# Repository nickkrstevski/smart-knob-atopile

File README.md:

# smart-knob
Shoutout to Scott Bezek for creating this awesome open source haptic feedback wheel!
https://github.com/scottbez1/smartknob.git

# atopile
>ato install smartknob

This package contains adaptations of the smart knob designs captured in atopile code. atopile will help with jellybean component selection, board layout, versioning, collaboration..

Upon importing the smart knob package into your atopile project, you will find a complete netlist and accompanying layout that can be merged or connected into a larger design. atopile's component selection integrates directly wih the JLC component supplier, generating build outputs that can be directly sent to JLC and show up at your door assembled.

For example, I am creating a chess clock that uses the smart knob as a dial, and adds some leds/capacitive touch sensors to build upon the original design/layout.
https://github.com/nickkrstevski/chess-clock

# Structure
The Smart Knob design consists of 2 PCBAs, a BLDC motor, an LCD, and plenty of mechanical bits holding everything together. This project will contain a Smart Knob module that has 2 build target modules, "SmartKnobBase", and "SmartKnobScreen"

## SmartKnobBase
- ESP32-S3
- USB-C
- BLDC Driver
- Strain Sensor
- Ambient Light Sensor
- Magnetic Quadrature Encoder

## SmartKnobScreen
- Backlight FET/ballast resistor
- LCD Connections

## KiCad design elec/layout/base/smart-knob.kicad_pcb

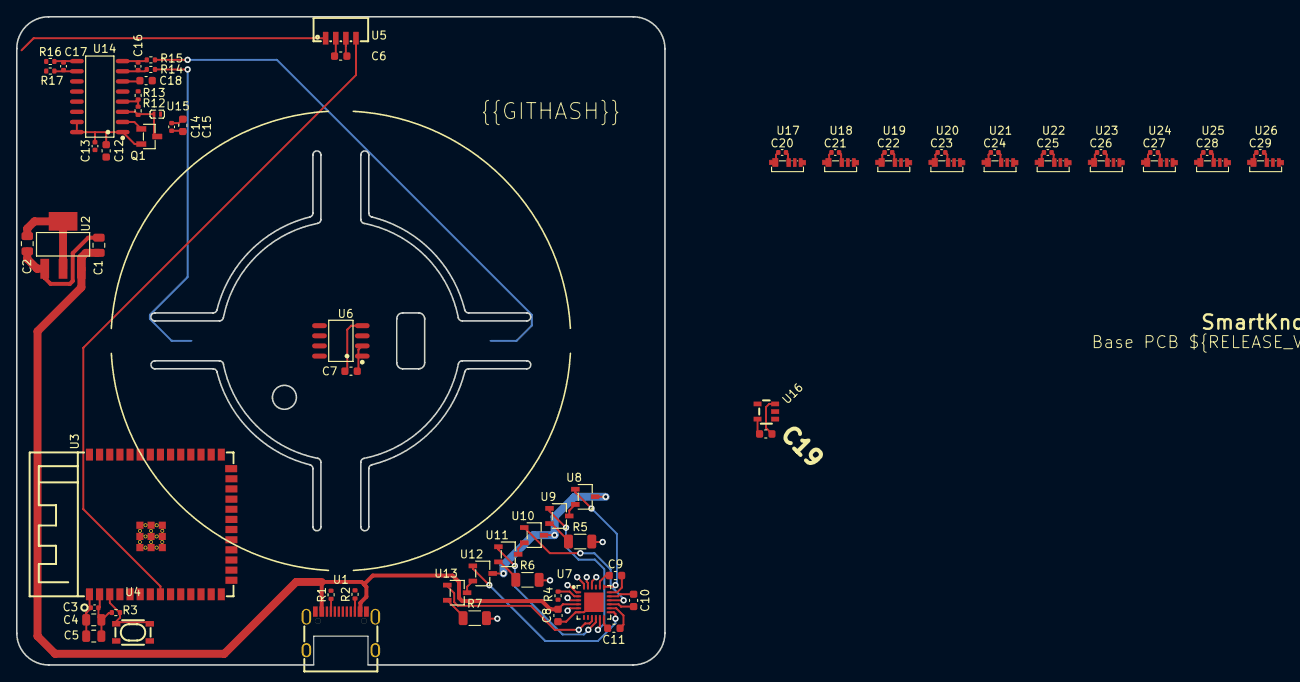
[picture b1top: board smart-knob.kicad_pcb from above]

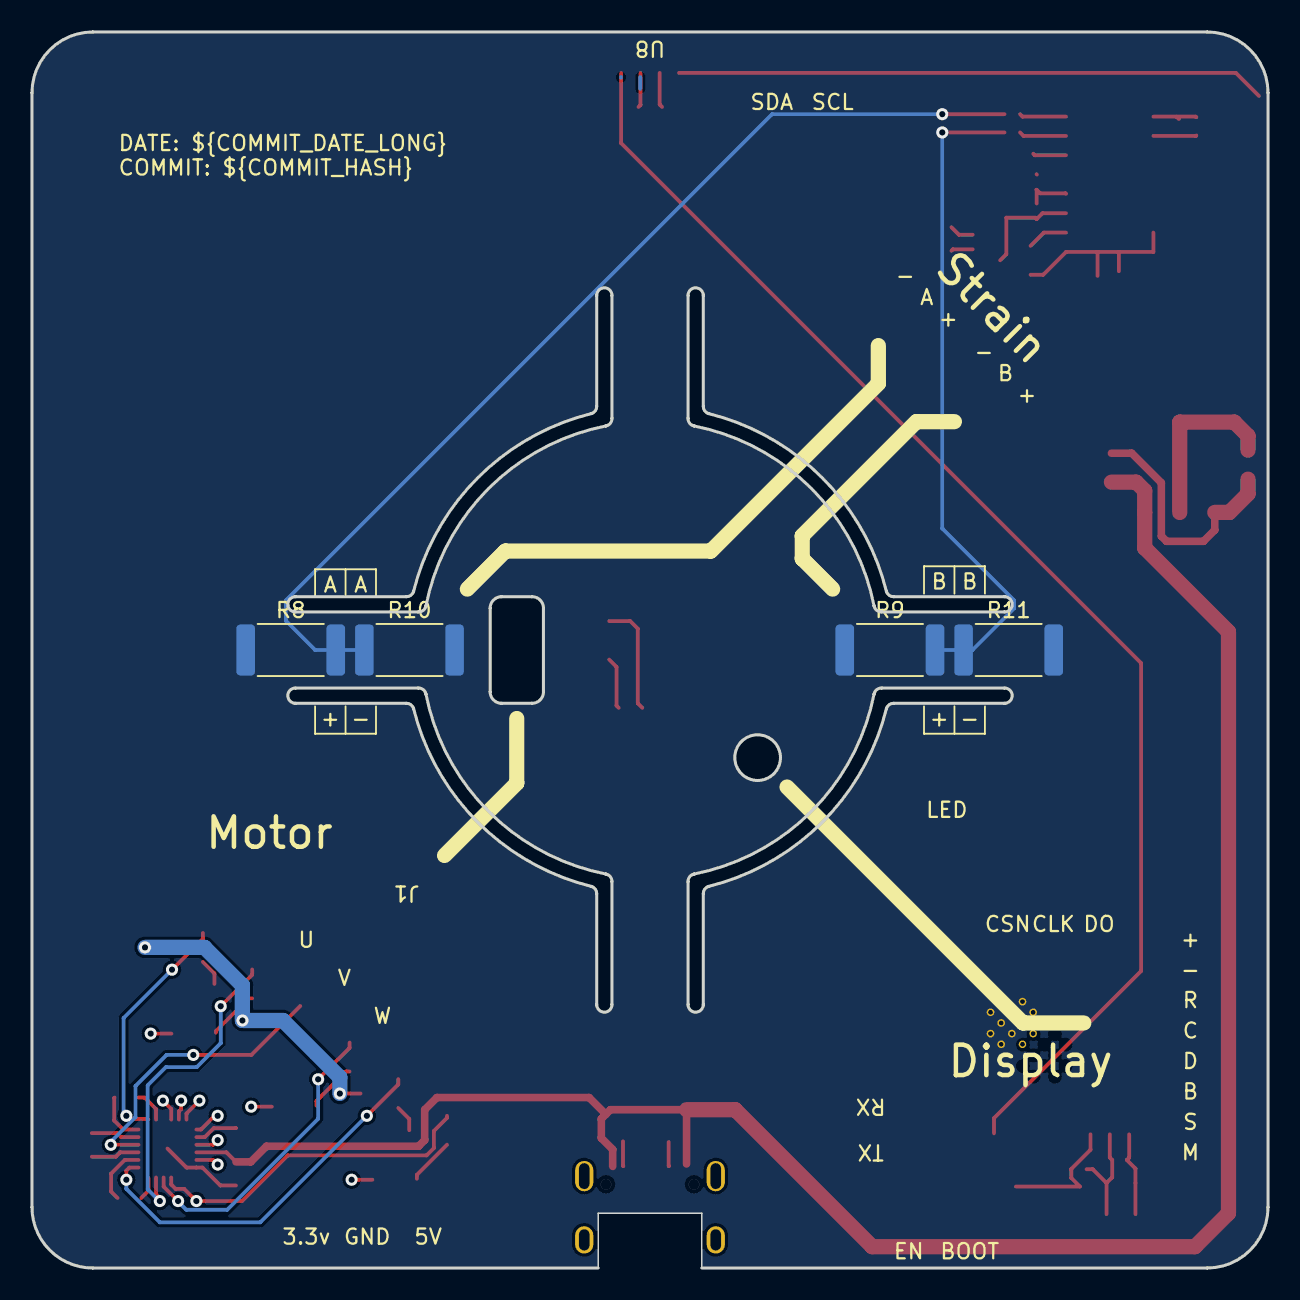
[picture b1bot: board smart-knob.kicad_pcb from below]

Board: 2 copper layers, 81.2 x 81.2 mm, 74 parts (4 on the bottom side), 64 nets.

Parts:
C1, C2, C4, C5: 25V 10uF X5R ±10% 0805 Multilayer Ceramic Capacit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; C0805
C3, C16, C17: 16V 100nF X7R ±10% 0402 Multilayer Ceramic Capaci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; C0402
C6, C7, C12, C15, C18, C19: 50V 100nF X7R ±10% 0603 Multilayer Ceramic Capaci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; C0603
C8, C9, C10, C11: 50V 1uF X5R ±10% 0603 Multilayer Ceramic Capacito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; C0603
C13, C14: 6.3V 10uF X5R ±20% 0402 Multilayer Ceramic Capaci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; C0402
C20, C21, C22, C23, C24, C25, C26, C27, C28, C29: 25V 1uF X5R ±10% 0402 Multilayer Ceramic Capacito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; C0402
Q1: SOT-23-3_L2.9-W1.3-P1.90-LS2.4-BR
R1, R2: 62.5mW Thick Film Resistors ±100ppm/℃ ±1% 5.1kΩ 0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; R0402
R3, R12: 62.5mW Thick Film Resistors ±100ppm/℃ ±1% 10kΩ 04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; R0402
R4: 62.5mW Thick Film Resistors ±100ppm/℃ ±1% 40.2kΩ 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; R0402
R5, R6, R7: 250mW Thick Film Resistors ±800ppm/℃ ±1% 1Ω 1206 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; R1206
R8, R9, R10, R11: 1W Thick Film Resistors ±100ppm/℃ ±5% 330Ω 2512 C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; R2512
R13: 62.5mW Thick Film Resistors ±100ppm/℃ ±1% 8.2kΩ 0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; R0402
R14, R15, R16, R17: 62.5mW Thick Film Resistors ±1% ±200ppm/℃ 100Ω 04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; R0402
U1: USB-C-SMD_KH-TYPE-C-16P
U2: SOT-223-3_L6.5-W3.4-P2.30-LS7.0-BR
U3: WIRELM-SMD_ESP32-S3-WROOM-1
U4: KEY-SMD_4P-L4.2-W3.2-P2.20-LS4.6
U5: SENSOR-SMD_EML7700-TT
U6: SOP-8_L4.9-W3.9-P1.27-LS6.0-BL
U7: VQFN-24_L4.0-W4.0-P0.50-TL-EP2.5
U8, U9, U10, U11, U12, U13: SOT-23-3_L2.9-W1.6-P1.90-LS2.8-BR
U14: SOP-16_L10.0-W3.9-P1.27-LS6.0-BL
U15: 3.3 +/- 0.99 (30%) microhenry; IND-SMD_L1.2-W0.7
U16: SOT-23-5_L2.9-W1.6-P0.95-LS2.8-BR
U17, U18, U19, U20, U21, U22, U23, U24, U25, U26: LED-SMD_4P-L4.0-W1.4_SK6805SIDE-S
Z5: dummy_keepouts; ViewKeepouts3d

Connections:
base: Q1.1, U14.2
cc1: R1.1, U1.A5
cc2: R2.1, U1.B5
clock: U3.38, U14.11
data: U3.31, U14.12
dm: U1.A7, U1.B7, U3.13
dp: U1.A6, U1.B6, U3.14
en: R3.2, U3.3, U4.1, U4.2
esp32s3.ic-sda: U3.8, U5.4
esp32s3.ic-sda-1: U3.7, U16.2
esp32s3.ic-vcc: U3.28, U7.3
esp32s3.ic-vcc-1: U3.26, U7.1
esp32s3.ic-vcc-2: U3.16, U7.22
esp32s3.ic-vcc-3: U3.11, U7.23
esp32s3.ic-vcc-4: R4.1, U3.10, U7.2
esp32s3.ic-vcc-5: U3.9, U7.24
gnd: R5.2, R6.2, R7.2
hba.nfet_low-source: R5.1, U9.2
hbb.nfet_low-source: R6.1, U11.2
hbc.nfet_low-source: R7.1, U13.2
inna: C16.2, R14.2, U14.7
innb: C17.2, R16.2, U14.9
inpa: C16.1, R15.2, U14.8
inpb: C17.1, R17.2, U14.10
io13: U3.21, U6.7
io14: U3.22, U6.8
io37: U3.30, U6.6
ldo3V3-vcc: C2.1, C3.1, C4.1, C5.1, C12.1, C13.1, Q1.2, R3.1, U2.2, U2.4, U3.2, U14.1, U14.15, U14.16
led1-vcc-1: U17.3, U18.4
led2-vcc: U18.3, U19.4
led3-vcc: U19.3, U20.4
led4-vcc: U20.3, U21.4
led5-vcc: U21.3, U22.4
led6-vcc: U22.3, U23.4
led7-vcc: U23.3, U24.4
led8-vcc: U24.3, U25.4
led9-vcc: U25.3, U26.4
light_sensor.ic-gnd: C6.2, U5.3
light_sensor.ic-vcc: C6.1, U5.2
n: R9.2, R11.1, R14.1
p: R8.2, R10.1, R15.1
phase_a: U8.2, U9.3
phase_b: U10.2, U11.3
phase_c: U12.2, U13.3
power_stage-vcc-1: U7.11, U9.1
power_stage-vcc-2: U7.10, U11.1
power_stage-vcc-3: U7.9, U13.1
power_stage-vcc-4: U7.19, U8.1
power_stage-vcc-5: U7.16, U10.1
power_stage-vcc-6: U7.13, U12.1
power_stage-vcc-7: C9.2, U7.18
power_stage-vcc-8: C10.2, U7.15
power_stage-vcc-9: C11.2, U7.12
power_stage.ic-vcc: C9.1, U7.20
power_stage.ic-vcc-1: C10.1, U7.17
power_stage.ic-vcc-2: C11.1, U7.14
scl: U3.12, U5.1
strain_adc.ic-vcc: Q1.3, R12.1, U14.3, U15.1
usbc-gnd: C1.2, C2.2, C3.2, C4.2, C5.2, C7.2, C8.2, C12.2, C13.2, C14.2, C15.2, C18.2, C19.2, C20.2, C21.2, C22.2, C23.2, C24.2, C25.2, C26.2, C27.2, C28.2, C29.2, R1.2, R2.2, R4.2, R10.2, R11.2, R13.2, U1.1, U1.2, U1.3, U1.4, U1.A1, U1.A12, U1.B1, U1.B12, U2.1, U3.1, U3.40, U3.41, U4.3, U4.4, U6.4, U7.6, U7.25, U14.5, U14.14, U16.3, U17.2, U18.2, U19.2, U20.2, U21.2, U22.2, U23.2, U24.2, U25.2, U26.2
usbc-vcc: C1.1, C7.1, C8.1, C19.1, C20.1, C21.1, C22.1, C23.1, C24.1, C25.1, C26.1, C27.1, C28.1, C29.1, U1.A4, U1.A9, U1.B4, U1.B9, U2.3, U6.1, U6.2, U7.4, U16.5, U17.1, U18.1, U19.1, U20.1, U21.1, U22.1, U23.1, U24.1, U25.1, U26.1
vbg: C18.1, U14.6
vcc: U8.3, U10.3, U12.3
vcc-1: C14.1, C15.1, R8.1, R9.1, U15.2
vfb: R12.2, R13.1, U14.4

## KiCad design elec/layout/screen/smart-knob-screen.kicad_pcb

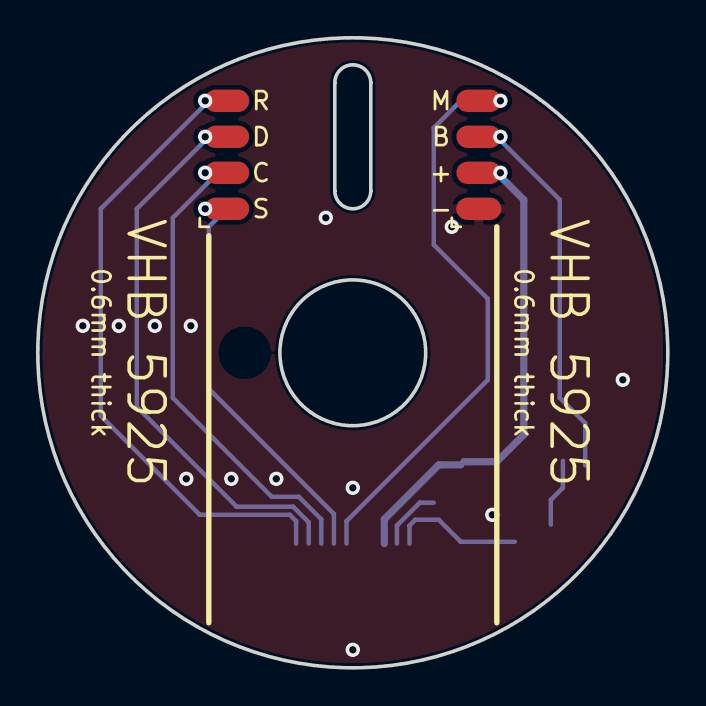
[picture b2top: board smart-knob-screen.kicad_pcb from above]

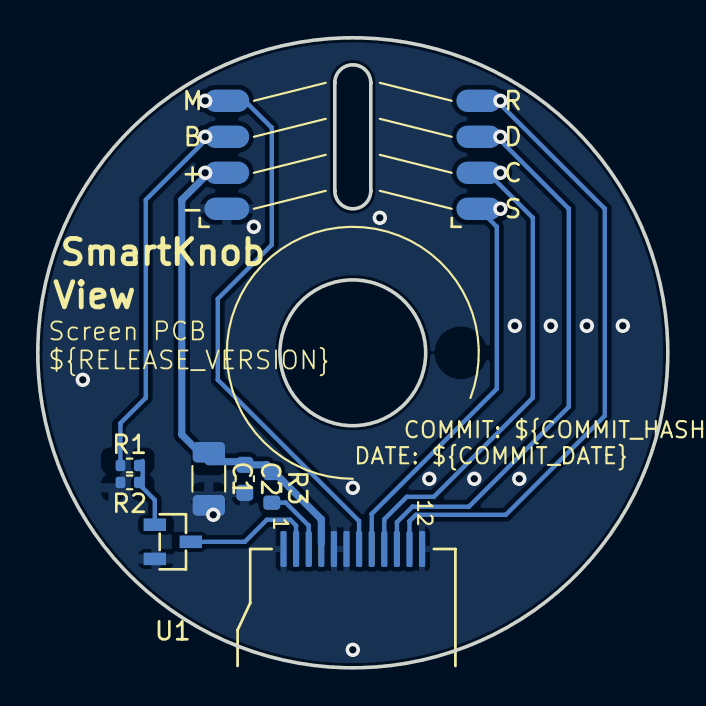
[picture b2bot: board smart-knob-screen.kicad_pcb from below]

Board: 2 copper layers, 35.0 x 35.0 mm, 11 parts (9 on the bottom side), 3 nets.

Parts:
C1: 25V 22uF X5R ±10% 1206 Multilayer Ceramic Capacit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; C1206
C2: 50V 100nF X7R ±10% 0603 Multilayer Ceramic Capaci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; C0603
J1, J3, J4, J5: Conn_01x04; SolderPads_2mm_4
J2: GC9A01; GC9A01Round1.28
R1: 62.5mW Thick Film Resistors ±100ppm/℃ ±1% 10kΩ 04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; R0402
R2: 62.5mW Thick Film Resistors ±100ppm/℃ ±1% 1MΩ 040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; R0402
R3: 100mW Thick Film Resistors ±100ppm/℃ ±1% 22Ω 0603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; R0603
U1: SOT-23-3_L2.9-W1.3-P1.90-LS2.4-BR

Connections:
gate: R1.2, R2.1, U1.1
gnd: C1.2, C2.2, R2.2, U1.2
vcc: C1.1, C2.1, R3.1

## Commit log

2024-02-18 Configure project
2024-02-19 building out modules
2024-02-21 base and screen implemented, need 2 conn bldc driver
2024-02-21 connected 10 leds
2024-02-23 just need motor driver
2024-02-28 she builds!
2024-02-28 building, added power stage and half bridges
2024-03-27 screen layout complete
2024-03-28 base layout 40% complete
2024-04-02 chugging thru layout

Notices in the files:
elec/layout/base/smart-knob.kicad_pcb:
Copyright 2021 Accelerated Designs. All rights reserved.
